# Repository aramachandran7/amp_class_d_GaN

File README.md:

# SEE `/master` BRANCH
yay GaN audio

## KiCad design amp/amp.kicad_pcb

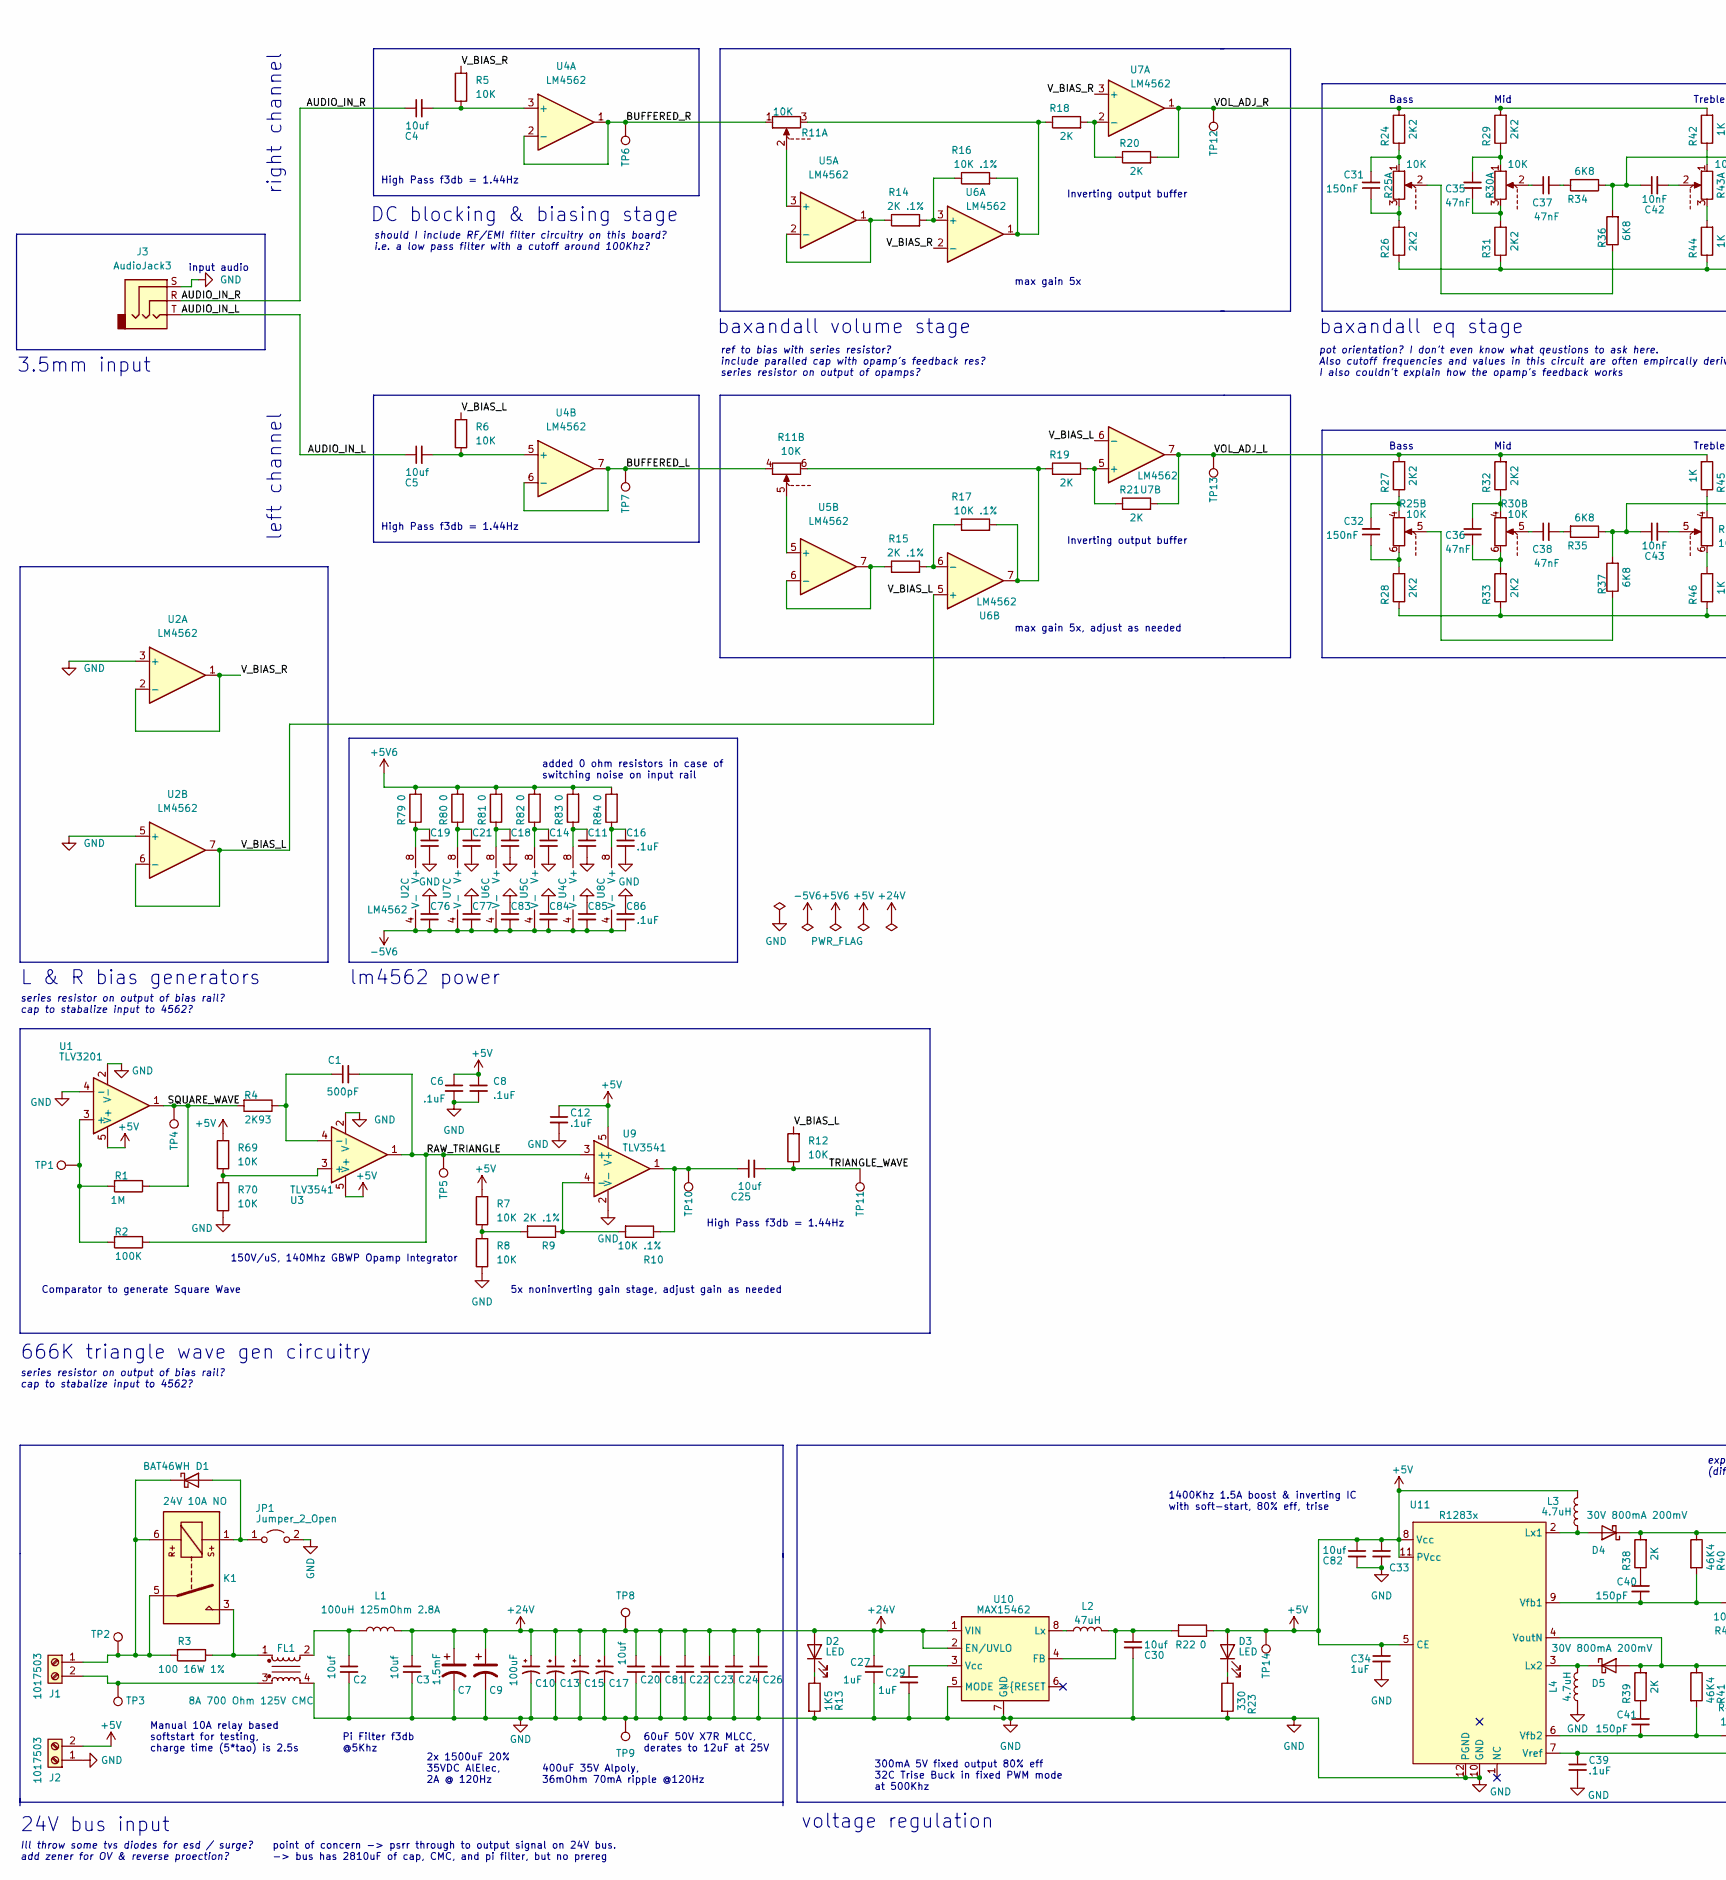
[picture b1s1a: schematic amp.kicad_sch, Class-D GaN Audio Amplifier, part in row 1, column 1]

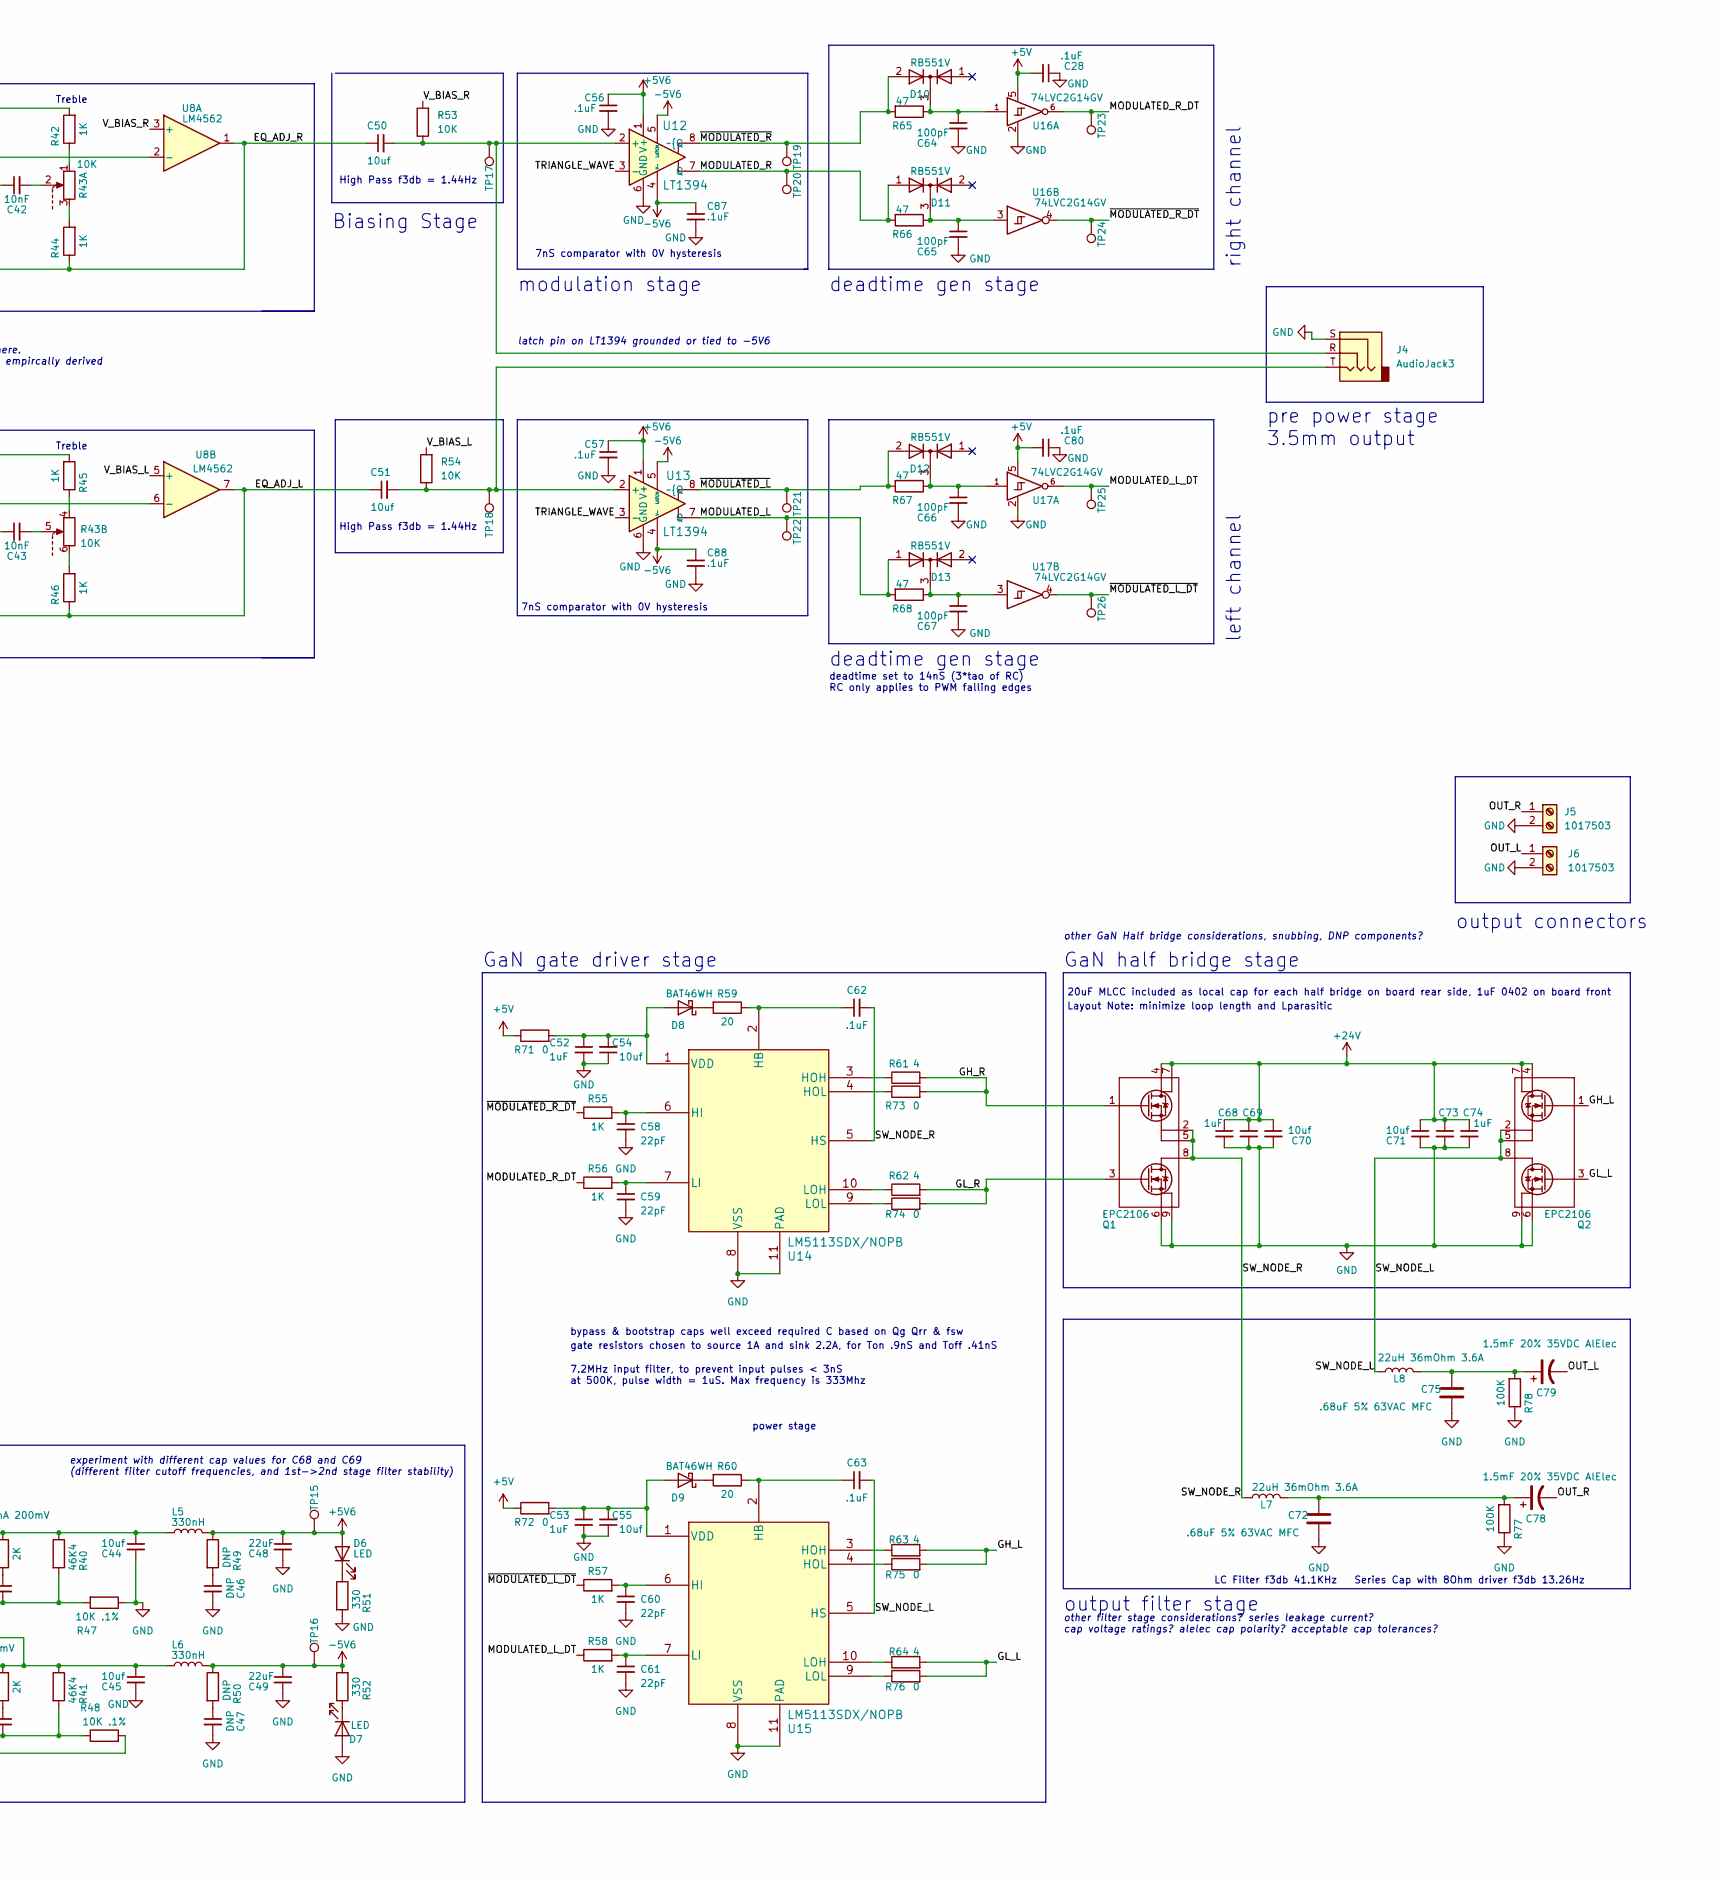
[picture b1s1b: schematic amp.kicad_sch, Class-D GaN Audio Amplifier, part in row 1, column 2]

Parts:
C1: 500pF; C_0603_1608Metric
C2, C3, C20, C22, C23, C24, C26, C81: 10uf; C_1206_3216Metric; MPN CL31A106MBHNNNE
C4, C5, C25, C30, C33, C44, C45, C50, C51, C54, C55, C69, C70, C71, C73, C82: 10uf; C_0805_2012Metric; MPN CL31A106MBHNNNE
C6, C8, C12, C28, C39, C56, C57, C62, C63, C80, C87, C88: .1uF; C_0402_1005Metric
C7, C9: 1.5mF; CP_Radial_D12.5mm_P5.00mm; MPN 35ZLH1500MEFC12.5X30
C10, C13, C15, C17: 100uF; C_Elec_8x10.2; MPN A768EB107M1ELAE036
C11, C14, C16, C18, C19, C21, C76, C77, C83, C84, C85, C86: .1uF; C_0603_1608Metric
C27, C29, C34, C52, C53, C68, C74: 1uF; C_0402_1005Metric; MPN CL21B105KBFNNNG
C31, C32: 150nF; C_0805_2012Metric
C35, C36, C37, C38: 47nF; C_0805_2012Metric
C40, C41: 150pF; C_0603_1608Metric; MPN CC0805KRX7R9BB151
C42, C43: 10nF; C_0805_2012Metric
C46, C47: DNP; C_0805_2012Metric; MPN CL21A226MAYNNNE
C48, C49: 22uF; C_0805_2012Metric; MPN CL21A226MAYNNNE
C58, C59, C60, C61: 22pF; C_0402_1005Metric; MPN CML0805C0G220JT50V
C64, C65, C66, C67: 100pF; C_0805_2012Metric
C72, C75: .68uF 5% 63VAC MFC; C_Radial_D5.0mm_H11.0mm_P2.00mm; MPN R82EC3680AA70J
C78, C79: 1.5mF 20% 35VDC AlElec; CP_Radial_D12.5mm_P5.00mm; MPN 35ZLH1500MEFC12.5X30
D1, D8, D9: BAT46WH; D_SOD-123F
D2, D3, D6, D7: LED; LED_0805_2012Metric_Pad1.15x1.40mm_HandSolder
D4, D5: 30V 800mA 200mV; D_SOD-323; MPN CUS08F30,H3F
D10, D11, D12, D13: RB551V; SOT-23; MPN RB551V-30TC_R1_00001
FL1: 8A 700 Ohm 125V CMC; ECMS1V1306-701-R
J1, J2, J5, J6: 1017503
J3, J4: AudioJack3; SJ-3523-SMT; MPN SJ-3523-SMT-TR
JP1: Jumper_2_Open; PinHeader_1x02_P2.54mm_Vertical
K1: 24V 10A NO; AZ9375-1A-24DEF; MPN AZ9375-1A-24DEF
L1: 100uH 125mOhm 2.8A; L_12x12mm_H8mm; MPN PA4320.104NLT
L2: 47uH; L_Vishay_IHLP-1616; MPN LQH44PH470MPRL
L3, L4: 4.7uH; L_0805_2012Metric_Pad1.15x1.40mm_HandSolder; MPN WLFM201609M4R7PC
L5, L6: 330nH; EXL1V0503-R33-R; MPN EXL1V0503-R33-R
L7, L8: 22uH 36mOhm 3.6A; L_10.4x10.4_H4.8; MPN NS10165T220MNA
Q1, Q2: EPC2106; epc2106
R1: 1M; R_0603_1608Metric
R2: 100K; R_0603_1608Metric
R3: 100 16W 1%; R_2512_6332Metric
R4: 2K93; R_0603_1608Metric
R5, R6, R53, R54: 10K; R_0805_2012Metric
R7, R8, R12, R69, R70: 10K; R_0603_1608Metric
R9: 2K .1%; R_0603_1608Metric
R10, R47, R48: 10K .1%; R_0603_1608Metric
R11, R25, R30, R43: 10K; PTA4544-2010CIB103; MPN PTA4544-2010CIB103_dual
R13: 1K5; R_0805_2012Metric
R14, R15: 2K .1%; R_0805_2012Metric
R16, R17: 10K .1%; R_0805_2012Metric
R18, R19, R20, R21: 2K; R_0805_2012Metric
R22: 0; R_0805_2012Metric
R23, R51, R52: 330; R_0805_2012Metric
R24, R26, R27, R28, R29, R31, R32, R33: 2K2; R_0805_2012Metric
R34, R35, R36, R37: 6K8; R_0805_2012Metric
R38, R39: 2K; R_0603_1608Metric
R40, R41: 46K4; R_0603_1608Metric
R42, R44, R45, R46: 1K; R_0805_2012Metric
R49, R50: DNP; R_0805_2012Metric
R55, R56, R57, R58: 1K; R_0402_1005Metric
R59, R60: 20; R_0402_1005Metric
R61, R62, R63, R64: 4; R_0402_1005Metric
R65, R66, R67, R68: 47; R_0805_2012Metric
R71, R72, R73, R74, R75, R76: 0; R_0402_1005Metric
R77, R78: 100K; R_0805_2012Metric
R79, R80, R81, R82, R83, R84: 0; R_0603_1608Metric
TP1, TP4, TP5, TP10, TP11, TP12, TP13, TP17, TP18, TP19, TP20, TP21, TP22, TP23, TP24, TP25, TP26: TestPoint; TestPoint_Pad_D1.0mm
TP2, TP3, TP6, TP7, TP8, TP9, TP14, TP15, TP16: TestPoint; TestPoint_Pad_2.5x2.5mm
U1: TLV3201; SOT-23-5; MPN TLV3201AIDBVR
U2, U4, U5, U6, U7, U8: LM4562; SOIC-8_3.9x4.9mm_P1.27mm
U3, U9: TLV3541; SOT-23-5; MPN TLV3541IDBVR
U10: MAX15462; DFN-8_2x2mm_P0.5mm; MPN MAX15462BATA+T
U11: R1283x; DFN-12-1EP_3x3mm_P0.5mm_EP1.6x2.5mm; MPN R1283K002C-TR
U12, U13: LT1394; LT1394CS8-PBF; MPN LT1394CS8-PBF
U14, U15: LM5113SDX/NOPB; LM5113SDX&slash_NOPB
U16, U17: 74LVC2G14GV; SOT-363_SC-70-6; MPN 74LVC2G14GV,125

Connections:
+5V: C6.1, C8.1, C12.1, C28.2, C33.1, C34.1, C80.2, C82.1, D3.2 (A), J2.2, L3.2, R7.2, R22.1, R69.2, R71.1, R72.1, TP14.1, U1.5 (V+), U3.5 (V+), U9.5 (V+), U11.5 (CE), U11.8 (Vcc), U11.11 (PVcc), U16.5 (VCC), U17.5 (VCC)
+5V6: C48.1, C56.1, C57.1, D6.2 (A), L5.2, R49.1, R79.2, R80.2, R81.2, R82.2, R83.2, R84.2, TP15.1, U12.1 (V+), U13.1 (V+)
+24V: C3.1, C7.1, C9.1, C10.1, C13.1, C15.1, C17.1, C20.1, C22.1, C23.1, C24.1, C26.1, C27.1, C68.1, C69.1, C70.1, C71.1, C73.1, C74.1, C81.1, D2.2 (A), L1.2, Q1.4, Q1.7, Q2.4, Q2.7, TP8.1, U10.1 (VIN), U10.2 (EN/UVLO)
-5V6: C49.1, C76.2, C77.2, C83.2, C84.2, C85.2, C86.2, C87.1, C88.1, L6.2, R50.1, R52.2, TP16.1, U2.4 (V-), U4.4 (V-), U5.4 (V-), U6.4 (V-), U7.4 (V-), U8.4 (V-), U12.4 (V-), U12.5 (LATCH), U13.4 (V-), U13.5 (LATCH)
/AUDIO_IN_L: C5.1, J3.T
/AUDIO_IN_R: C4.1, J3.R
/BUFFERED_L: R11.4, TP7.1, U4.6 (-), U4.7
/BUFFERED_R: R11.1, TP6.1, U4.1, U4.2 (-)
/EQ_ADJ_L: C51.1, R28.1, R33.1, R46.1, U8.7
/EQ_ADJ_R: C50.1, R26.1, R31.1, R44.1, U8.1
/GH_L: Q2.1, R63.2, R75.2
/GH_R: Q1.1, R61.2, R73.2
/GL_L: Q2.3, R64.2, R76.2
/GL_R: Q1.3, R62.2, R74.2
/MODULATED_L: D13.1, R68.2, TP22.1, U13.7 (Q)
/MODULATED_L_DT: R58.1, TP25.1, U17.6
/MODULATED_R: D11.1, R66.2, TP20.1, U12.7 (Q)
/MODULATED_R_DT: R56.1, TP23.1, U16.6
/OUT_L: C79.2, J6.1
/OUT_R: C78.2, J5.1
/RAW_TRIANGLE: C1.2, R2.1, TP5.1, U3.1, U9.3 (+)
/SQUARE_WAVE: R1.1, R4.2, TP4.1, U1.1
/SW_NODE_L: C63.2, L8.1, Q2.2, Q2.5, Q2.8, U15.5 (HS)
/SW_NODE_R: C62.2, L7.1, Q1.2, Q1.5, Q1.8, U14.5 (HS)
/TRIANGLE_WAVE: C25.2, R12.1, TP11.1, U12.3 (-), U13.3 (-)
/VOL_ADJ_L: R21.2, R27.2, R32.2, R45.2, TP13.1, U7.7
/VOL_ADJ_R: R20.2, R24.2, R29.2, R42.2, TP12.1, U7.1
/V_BIAS_L: R6.2, R12.2, R54.2, U2.6 (-), U2.7, U6.5 (+), U7.6 (-), U8.5 (+)
/V_BIAS_R: R5.2, R53.2, U2.1, U2.2 (-), U6.2 (-), U7.3 (+), U8.3 (+)
/~MODULATED_L_DT: R57.1, TP26.1, U17.4
/~MODULATED_L: D12.2, R67.2, TP21.1, U13.8 (~{Q)
/~MODULATED_R_DT: R55.1, TP24.1, U16.4
/~MODULATED_R: D10.2, R65.2, TP19.1, U12.8 (~{Q)
GND: C2.2, C3.2, C6.2, C7.2, C8.2, C9.2, C10.2, C11.2, C12.2, C13.2, C14.2, C15.2, C16.2, C17.2, C18.2, C19.2, C20.2, C21.2, C22.2, C23.2, C24.2, C26.2, C27.2, C28.1, C29.2, C30.2, C33.2, C34.2, C39.2, C44.2, C45.2, C46.2, C47.2, C48.2, C49.2, C52.2, C53.2, C54.1, C55.1, C56.2, C57.2, C58.2, C59.2, C60.2, C61.2, C64.2, C65.2, C66.2, C67.2, C68.2, C69.2, C70.2, C71.2, C72.2, C73.2, C74.2, C75.2, C76.1, C77.1, C80.1, C81.2, C82.2, C83.1, C84.1, C85.1, C86.1, C87.2, C88.2, D7.2 (A), FL1.4, J2.1, J3.S, J4.S, J5.2, J6.2, JP1.2 (B), L4.1, Q1.6, Q1.9, Q2.6, Q2.9, R8.1, R13.2, R23.2, R47.1, R51.2, R70.1, R77.1, R78.1, TP9.1, U1.2 (V-), U1.4 (-), U2.3 (+), U2.5 (+), U3.2 (V-), U9.2 (V-), U10.5 (MODE), U10.7 (GND), U11.10 (GND), U11.12 (PGND), U11.13, U12.6 (GND), U13.6 (GND), U14.8 (VSS), U14.11 (PAD), U15.8 (VSS), U15.11 (PAD), U16.2 (GND), U17.2 (GND)
unnamed: C1.1, R4.1, U3.4 (-)
unnamed: C2.1, FL1.2, L1.1
unnamed: C4.2, R5.1, U4.3 (+)
unnamed: C5.2, R6.1, U4.5 (+)
unnamed: C11.1, R83.1, U4.8 (V+)
unnamed: C14.1, R82.1, U5.8 (V+)
unnamed: C16.1, R84.1, U8.8 (V+)
unnamed: C18.1, R81.1, U6.8 (V+)
unnamed: C19.1, R79.1, U2.8 (V+)
unnamed: C21.1, R80.1, U7.8 (V+)
unnamed: C25.1, R10.1, TP10.1, U9.1
unnamed: C29.1, U10.3 (Vcc)
unnamed: C30.1, L2.2, R22.2, U10.4 (FB)
unnamed: C31.1, R25.3, R26.2
unnamed: C31.2, R24.1, R25.1
unnamed: C32.1, R25.6, R28.2
unnamed: C32.2, R25.4, R27.1
unnamed: C35.1, R29.1, R30.1
unnamed: C35.2, R30.3, R31.2
unnamed: C36.1, R30.4, R32.1
unnamed: C36.2, R30.6, R33.2
unnamed: C37.1, R30.2
unnamed: C37.2, R34.2
unnamed: C38.1, R30.5
unnamed: C38.2, R35.2
unnamed: C39.1, R48.2, U11.7 (Vref)
unnamed: C40.1, R38.1
unnamed: C40.2, R40.2, R47.2, U11.9 (Vfb1)
unnamed: C41.1, R39.1
unnamed: C41.2, R41.2, R48.1, U11.6 (Vfb2)
unnamed: C42.1, R34.1, R36.2, U8.2 (-)
unnamed: C42.2, R43.2
unnamed: C43.1, R35.1, R37.2, U8.6 (-)
unnamed: C43.2, R43.5
unnamed: C44.1, D4.1 (K), L5.1, R38.2, R40.1
unnamed: C45.1, D5.2 (A), L6.1, R39.2, R41.1, U11.4 (VoutN)
unnamed: C46.1, R49.2
unnamed: C47.1, R50.2
unnamed: C50.2, J4.R, R53.1, TP17.1, U12.2 (+)
unnamed: C51.2, J4.T, R54.1, TP18.1, U13.2 (+)
unnamed: C52.1, C54.2, D8.2 (A), R71.2, U14.1 (VDD)
unnamed: C53.1, C55.2, D9.2 (A), R72.2, U15.1 (VDD)
unnamed: C58.1, R55.2, U14.6 (HI)
unnamed: C59.1, R56.2, U14.7 (LI)
unnamed: C60.1, R57.2, U15.6 (HI)
unnamed: C61.1, R58.2, U15.7 (LI)
unnamed: C62.1, R59.1, U14.2 (HB)
unnamed: C63.1, R60.1, U15.2 (HB)
unnamed: C64.1, D10.3, R65.1, U16.1
unnamed: C65.1, D11.3, R66.1, U16.3
unnamed: C66.1, D12.3, R67.1, U17.1
unnamed: C67.1, D13.3, R68.1, U17.3
unnamed: C72.1, C78.1, L7.2, R77.2
unnamed: C75.1, C79.1, L8.2, R78.2
unnamed: D1.1 (K), J1.1, K1.5, K1.6, R3.2, TP2.1
unnamed: D1.2 (A), JP1.1 (A), K1.1
unnamed: D2.1 (K), R13.1
unnamed: D3.1 (K), R23.1
unnamed: D4.2 (A), L3.1, U11.2 (Lx1)
unnamed: D5.1 (K), L4.2, U11.3 (Lx2)
unnamed: D6.1 (K), R51.1
unnamed: D7.1 (K), R52.1
unnamed: D8.1 (K), R59.2
unnamed: D9.1 (K), R60.2
unnamed: FL1.1, K1.3, R3.1
unnamed: FL1.3, J1.2, TP3.1
unnamed: L2.1, U10.8 (Lx)
unnamed: R1.2, R2.2, TP1.1, U1.3 (+)
unnamed: R7.1, R8.2, R9.2
unnamed: R9.1, R10.2, U9.4 (-)
unnamed: R11.2, U5.3 (+)
unnamed: R11.3, R16.2, R18.1, U6.1
unnamed: R11.5, U5.5 (+)
unnamed: R11.6, R17.2, R19.1, U6.7
unnamed: R14.1, U5.1, U5.2 (-)
unnamed: R14.2, R16.1, U6.3 (+)
unnamed: R15.1, U5.6 (-), U5.7
unnamed: R15.2, R17.1, U6.6 (-)
unnamed: R18.2, R20.1, U7.2 (-)
unnamed: R19.2, R21.1, U7.5 (+)
unnamed: R25.2, R36.1
unnamed: R25.5, R37.1
unnamed: R42.1, R43.1
unnamed: R43.3, R44.2
unnamed: R43.4, R45.1
unnamed: R43.6, R46.2
unnamed: R61.1, U14.3 (HOH)
unnamed: R62.1, U14.10 (LOH)
unnamed: R63.1, U15.3 (HOH)
unnamed: R64.1, U15.10 (LOH)
unnamed: R69.1, R70.2, U3.3 (+)
unnamed: R73.1, U14.4 (HOL)
unnamed: R74.1, U14.9 (LOL)
unnamed: R75.1, U15.4 (HOL)
unnamed: R76.1, U15.9 (LOL)

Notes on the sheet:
Comparator to generate Square Wave
pot orientation? I don't even know what qeustions to ask here. Also cutoff frequencies and values in this circuit are often empircally derived I also couldn't explain how the opamp's feedback works
left channel
max gain 5x
Treble
deadtime gen stage
High Pass f3db = 1.44Hz
voltage regulation
150V/uS, 140Mhz GBWP Opamp Integrator
Ill throw some tvs diodes for esd / surge? add zener for OV & reverse proection?
modulation stage
baxandall volume stage
666K triangle wave gen circuitry
right channel
2x 1500uF 20% 35VDC AlElec, 2A @ 120Hz
Pi Filter f3db @5Khz
latch pin on LT1394 grounded or tied to -5V6
series resistor on output of bias rail? cap to stabalize input to 4562?
power stage
3.5mm input
5x noninverting gain stage, adjust gain as needed
other filter stage considerations? series leakage current? cap voltage ratings? alelec cap polarity? acceptable cap tolerances?
max gain 5x, adjust as needed
L & R bias generators
60uF 50V X7R MLCC, derates to 12uF at 25V
24V bus input
ref to bias with series resistor? include paralled cap with opamp's feedback res? series resistor on output of opamps?
deadtime set to 14nS (3*tao of RC) RC only applies to PWM falling edges
LC Filter f3db 41.1KHz
Inverting output buffer
Bass
7nS comparator with 0V hysteresis
GaN half bridge stage
gate resistors chosen to source 1A and sink 2.2A, for Ton .9nS and Toff .41nS
Layout Note: minimize loop length and Lparasitic
point of concern -> psrr through to output signal on 24V bus. -> bus has 2810uF of cap, CMC, and pi filter, but no prereg
Series Cap with 8Ohm driver f3db 13.26Hz
output connectors
300mA 5V fixed output 80% eff 32C Trise Buck in fixed PWM mode at 500Khz
experiment with different cap values for C68 and C69 (different filter cutoff frequencies, and 1st->2nd stage filter stability)

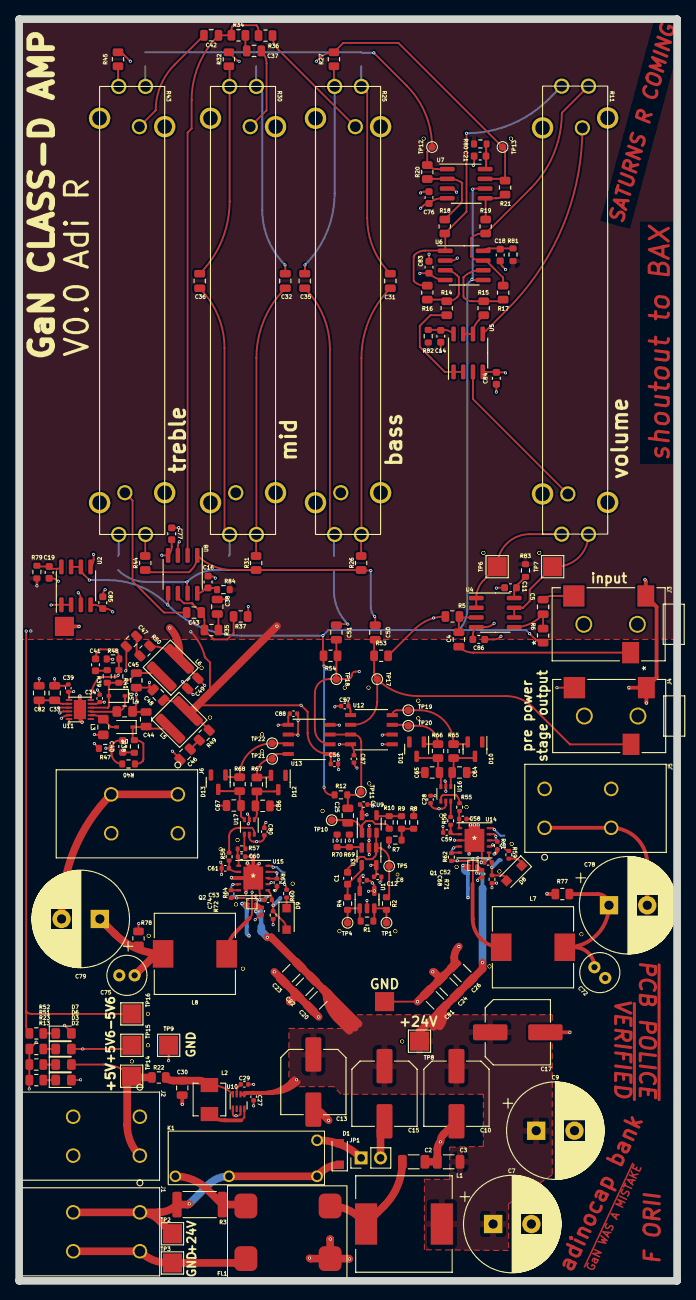
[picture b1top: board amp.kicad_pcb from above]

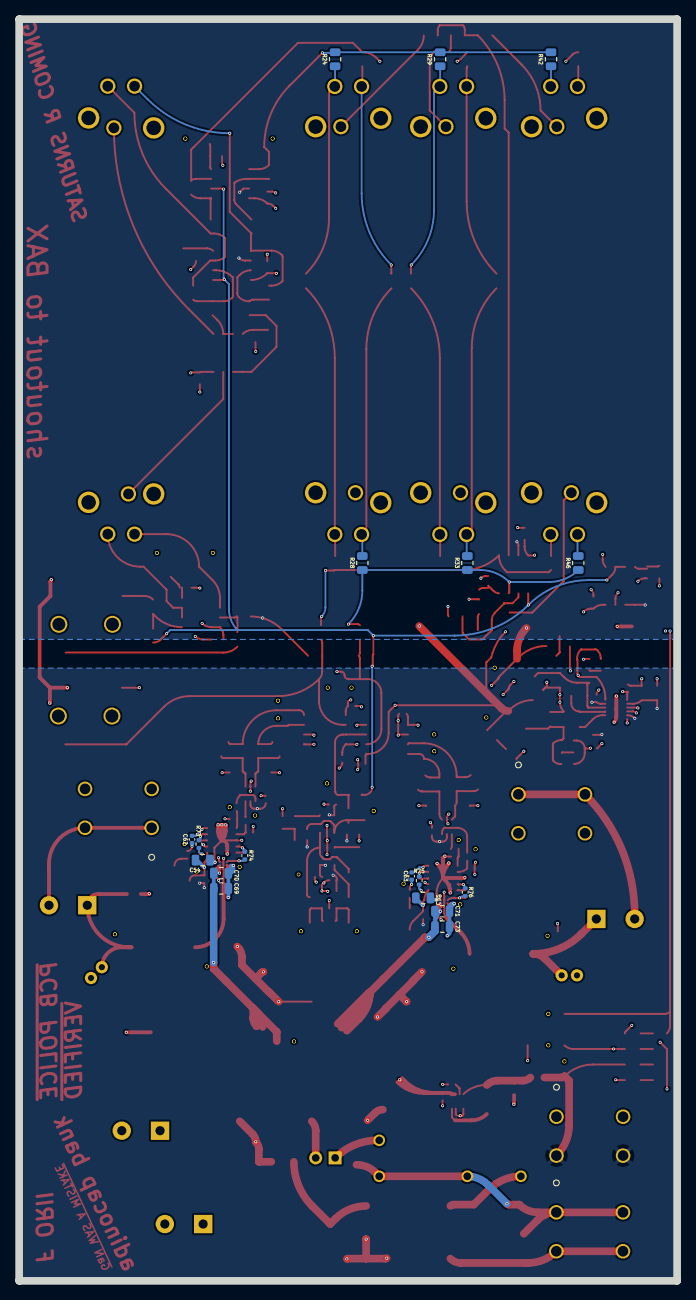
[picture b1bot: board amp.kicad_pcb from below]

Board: 4 copper layers, 85.9 x 164.8 mm, 243 parts (18 on the bottom side), 129 nets.

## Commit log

2022-11-10 schem first pass
2023-01-18 lots of schem and layouts updates
2023-02-12 shipped rev0 hardware
2023-02-12 schem pdf
